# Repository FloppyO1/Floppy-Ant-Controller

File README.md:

# Floppy Ant Controller

The Floppy Ant Controller is a control board for Antweight (150g) fighting robots. It implements many features and thanks to the ability to change settings without having to modify the code it makes it perfect for less experienced people.

Taking inspiration from the now well-known Malenki nano (https://github.com/MarkR42/malenki-nano.git), other features have been added, maintaining a small size and an affordable price.

## Features

- 3x DC motors driver (1000 speed steps);
- 2x servo outputs (one of which can be selected with a soldering jumper if 5V or HV from the battery);
- 200Hz servo frequency;
- BEC 5V 3A max;
- 2x expansion ports with possible digital or analog readout (e.g. potentiometers, switches etc.);
- Support for 1 and 2s batteries;
- Battery voltage readout, with settable weapon speed limitation threshold & cutoff threshold (indipendent);
- Settings can be set via USB with dedicated software or serial terminal;
- 4 channels PWM, and 8 channels PPM compatibility;
- Dimensions of 23mm*33mm for a weight of 2.9g.

## Last hardware version notes (V1.3)
In the latest version (V1.3), problems with errors in the schematic were fixed, specifically a capacitor in the Buck Converter that prevented it from functioning correctly.

Compared to version 1.2, the battery and switch connections have been moved, because in their previous position they were too close to the receiver connections, so there was a risk of short circuits and burning out the entire 3.3V part (which happened to me😢).

## Software notes:

The FAC settings tool has been completely rewritten, this time not using phython and pysimplegui (which I discovered ask for a monthly fee to be distributed 😑).

This new version, signed with the 2.0 signature, is much more stable and looks better in my opinion. Like the previous version, it allows you to export and import all your settings in a .csv file for easy sharing.

## Support this project with a donation

To support this project you can make a donation via PayPal or buy a Floppy Ant Controller:

- https://www.paypal.com/paypalme/floppylab

- https://ko-fi.com/floppylab

## License
[CERN Open Hardware Licence Version 2 - Strongly Reciprocal](https://choosealicense.com/licenses/cern-ohl-s-2.0/#)

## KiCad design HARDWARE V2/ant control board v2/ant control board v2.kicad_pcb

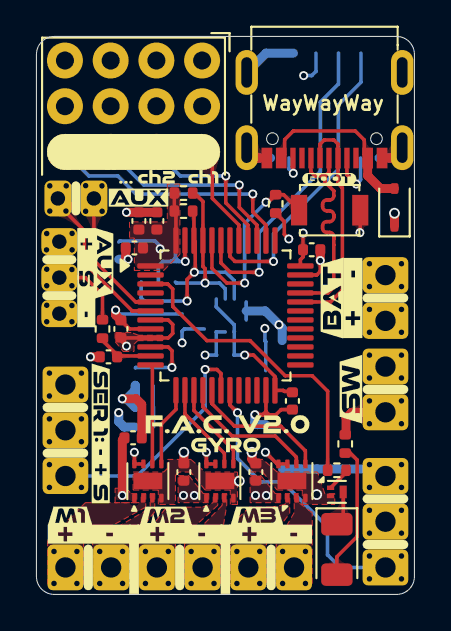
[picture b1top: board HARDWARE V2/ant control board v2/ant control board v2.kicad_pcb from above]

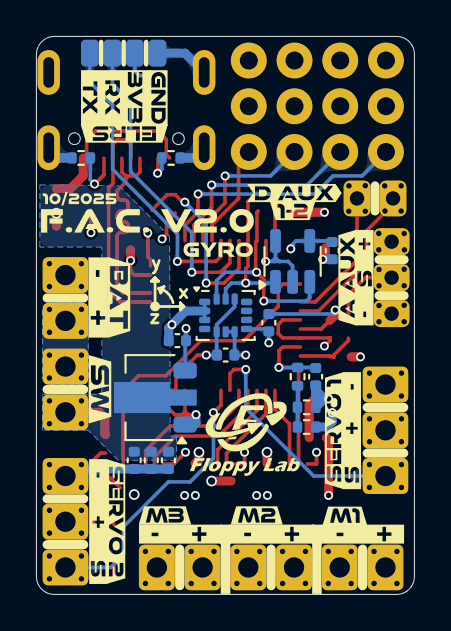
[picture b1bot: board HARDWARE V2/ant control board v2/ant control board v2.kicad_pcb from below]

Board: 4 copper layers, 21.0 x 31.0 mm, 96 parts (42 on the bottom side), 42 nets.

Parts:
C1, C2, C3, C4, C5, C6, C7, C8, C13: 4.7u; C_0402_1005Metric
C9, C10, C11, C14, C15, C16, C17, C18, C19: 100n; C_0402_1005Metric
D1: 1N5819WS; D_SOD-323
D2: STATUS; LED_1206_3216Metric
J1: SWITCH; 01x02_TH_pad_renforced
J2: 2s Battery; 01x02_TH_pad_renforced
J3: USB-C_304A-ACP16X; USB_C_304A-ACP16X
J4: M1; 01x02_TH_pad_renforced
J5: M2; 01x02_TH_pad_renforced
J6: M3; 01x02_TH_pad_renforced
J7: servo 1; 01x03_TH_pad_renforced
J8: servo 2; 01x03_TH_pad_renforced
J9: ADC_AUX; 01x03_TH_pad_renforced_small
J10: DIGITAL_AUX; 01x02_TH_pad_renforced_small
J12: ELRS; Pad 01x04 small
Q1: NMOS; Diodes_DFN1006-3
R1, R2, R6, R7, R8, R9, R10: 5.1k; R_0402_1005Metric
R3, R5: 10k; R_0402_1005Metric
R4, R11: 1.5k; R_0402_1005Metric
SW1: BOOT; SW_SPST_B3U-1000P
U1: GM7333; SOT-89-3
U2, U3, U4: DRV8837; WSON-8-1EP_2x2mm_P0.5mm_EP0.9x1.6mm
U5: LSM6DS3; LGA-14_3x2.5mm_P0.5mm_LayoutBorder3x4y
U6: STM32F072CBTx; LQFP-48_7x7mm_P0.5mm
U7: FS2A 4CH reciever
U8: AT24C02C; SOT-23-5
kibuzzard-68CD6E18, kibuzzard-68CD6E18#2: G***; kibuzzard-68CD6E18
kibuzzard-68CD6E40: G***; kibuzzard-68CD6E40
kibuzzard-68CD6E53, kibuzzard-68CD6E53#2: G***; kibuzzard-68CD6E53
kibuzzard-68CD7A1F: G***; kibuzzard-68CD7A1F
kibuzzard-68CD7CD9, kibuzzard-68CD7CD9#2: G***; kibuzzard-68CD7CD9
kibuzzard-68CD71AA, kibuzzard-68CD71AA#2: G***; kibuzzard-68CD71AA
kibuzzard-68CD73CB: G***; kibuzzard-68CD73CB
kibuzzard-68CD73D1: G***; kibuzzard-68CD73D1
kibuzzard-68CD78A4: G***; kibuzzard-68CD78A4
kibuzzard-68CD78BE: G***; kibuzzard-68CD78BE
kibuzzard-68CD78F0: G***; kibuzzard-68CD78F0
kibuzzard-68CD79A4: G***; kibuzzard-68CD79A4
kibuzzard-68CD79BE: G***; kibuzzard-68CD79BE
kibuzzard-68CD717E: G***; kibuzzard-68CD717E
kibuzzard-68CD725D, kibuzzard-68CD725D#2: G***; kibuzzard-68CD725D
kibuzzard-68CD756A: G***; kibuzzard-68CD756A
kibuzzard-68CD769D: G***; kibuzzard-68CD769D
kibuzzard-68CD784B: G***; kibuzzard-68CD784B
kibuzzard-68CD787F: G***; kibuzzard-68CD787F
kibuzzard-68CD793B: G***; kibuzzard-68CD793B
kibuzzard-68CD795A: G***; kibuzzard-68CD795A
kibuzzard-68CD7254, kibuzzard-68CD7254#2: G***; kibuzzard-68CD7254
kibuzzard-68CD7457: G***; kibuzzard-68CD7457
kibuzzard-68CD7642: G***; kibuzzard-68CD7642
kibuzzard-68CFBDBE: G***; kibuzzard-68CFBDBE
kibuzzard-68CFBDCF: G***; kibuzzard-68CFBDCF
kibuzzard-68CFBDD6: G***; kibuzzard-68CFBDD6
kibuzzard-68CFBE33: G***; kibuzzard-68CFBE33
kibuzzard-68CFBFAF: G***; kibuzzard-68CFBFAF
kibuzzard-68CFBFFE: G***; kibuzzard-68CFBFFE
kibuzzard-68CFC012: G***; kibuzzard-68CFC012
kibuzzard-68CFC153: G***; kibuzzard-68CFC153
kibuzzard-68CFCF3D: G***; kibuzzard-68CFCF3D
kibuzzard-68CFCF36: G***; kibuzzard-68CFCF36
kibuzzard-68CFCF49: G***; kibuzzard-68CFCF49
kibuzzard-68CFD0CD: G***; kibuzzard-68CFD0CD
kibuzzard-68CFD0E9: G***; kibuzzard-68CFD0E9
kibuzzard-6901144A: G***; kibuzzard-6901144A

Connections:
+3V3: C4.1, C9.1, C10.1, C13.1, C14.1, C15.1, C16.1, C17.1, C18.1, C19.1, J9.1, J12.3, R8.2, R9.2, SW1.1, U1.3 (OUT), U2.7 (~SLEEP), U2.8 (VCC), U3.7 (~SLEEP), U3.8 (VCC), U4.7 (~SLEEP), U4.8 (VCC), U5.5 (VDDIO), U5.8 (VDD), U5.12 (CS), U6.1 (VBAT), U6.7 (NRST), U6.9 (VDDA), U6.24 (VDD), U6.36 (VDDIO2), U6.48 (VDD), U7.2 (VCC), U7.5, U7.8, U7.11, U8.4 (VCC)
+BATT: C1.1, C2.1, C3.1, C5.1, C6.1, C7.1, D1.1 (K), J1.2, J7.2, J8.2, R3.1, R11.2, U1.2 (IN), U2.1 (VM), U3.1 (VM), U4.1 (VM)
/DC Motors/M1+: J4.1, U2.2 (OUT1)
/DC Motors/M1-: J4.2, U2.3 (OUT2)
/DC Motors/M2+: J5.1, U3.2 (OUT1)
/DC Motors/M2-: J5.2, U3.3 (OUT2)
/DC Motors/M3+: J6.1, U4.2 (OUT1)
/DC Motors/M3-: J6.2, U4.3 (OUT2)
/DC Motors/PWM_M1_B: U2.5 (IN2), U6.13 (PA3)
/DC Motors/PWM_M1_F: U2.6 (IN1), U6.12 (PA2)
/DC Motors/PWM_M2_B: U3.5 (IN2), U6.15 (PA5)
/DC Motors/PWM_M2_F: U3.6 (IN1), U6.14 (PA4)
/DC Motors/PWM_M3_B: U4.5 (IN2), U6.17 (PA7)
/DC Motors/PWM_M3_F: U4.6 (IN1), U6.16 (PA6)
/MCU and RX/ADC1: C11.2, R6.2, U6.11 (ADC_IN1)
/MCU and RX/BOOT0: R7.1, SW1.2, U6.44 (BOOT0)
/MCU and RX/CH1_PPM: U6.41 (PB5), U7.3 (CH1_(PPM))
/MCU and RX/CH2: U6.40 (PB4), U7.6 (CH2)
/MCU and RX/CH3: U6.39 (PB3), U7.9 (CH3)
/MCU and RX/CH4: U6.38 (PA15), U7.12 (CH4)
/MCU and RX/DIGITAL_AUX1: J10.1, U6.5 (PF0)
/MCU and RX/DIGITAL_AUX2: J10.2, U6.6 (PF1)
/MCU and RX/I2C1_SCL: R9.1, U5.13 (SCL), U6.45 (I2C1_SCL), U8.1 (SCL)
/MCU and RX/I2C1_SDA: R8.1, U5.14 (SDA), U6.46 (I2C1_SDA), U8.3 (SDA)
/MCU and RX/SERVO1: J7.1, U6.18 (PB0)
/MCU and RX/SERVO2: J8.1, U6.19 (PB1)
/MCU and RX/STATUS_LED: R10.1, U6.3 (PC14)
/MCU and RX/UART2_RX: J12.2, U6.43 (USART1_RX)
/MCU and RX/UART2_TX: J12.1, U6.42 (USART1_TX)
/MCU and RX/USB_D+: J3.6 (DP1), J3.8 (DP2), U6.33 (USB_DP)
/MCU and RX/USB_D-: J3.5 (DN2), J3.7 (DN1), U6.32 (USB_DM)
/MCU and RX/VBAT: C8.2, R5.2, U6.10 (ADC_IN0)
/Power/+SW: J1.1, J2.2
/Power/VUSB: D1.2 (A), J3.2 (VBUS), J3.11 (VBUS)
/Sensors/VBAT_DIV: R3.2, R4.1, R5.1
GND: C1.2, C2.2, C3.2, C4.2, C5.2, C6.2, C7.2, C8.1, C9.2, C10.2, C11.1, C13.2, C14.2, C15.2, C16.2, C17.2, C18.2, C19.2, J2.1, J3.1 (GND_1), J3.12 (GND_2), J3.13 (SHIELD), J7.3, J8.3, J9.3, J12.4, Q1.2 (S), R1.2, R2.2, R4.2, R7.2, U1.1 (GND), U2.4 (GND), U2.9 (GND), U3.4 (GND), U3.9 (GND), U4.4 (GND), U4.9 (GND), U5.1 (SDO/SA0), U5.2 (SDX), U5.3 (SCX), U5.6 (GND), U5.7 (GND), U6.8 (VSSA), U6.23 (VSS), U6.35 (VSS), U6.47 (VSS), U7.1 (GND), U7.4, U7.7, U7.10, U8.2 (GND), U8.5 (WP)
unnamed: D2.2 (A), R11.1
unnamed: D2.1 (K), Q1.3 (D)
unnamed: J3.4 (CC1), R2.1
unnamed: J3.10 (CC2), R1.1
unnamed: J9.2, R6.1
unnamed: Q1.1 (G), R10.2

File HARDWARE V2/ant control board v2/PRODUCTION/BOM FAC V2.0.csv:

"Reference","Value","LCSC","Footprint","Qty"
"U8","AT24C02C","C7432363","Package_TO_SOT_SMD:SOT-23-5","1"
"J3","USB-C_304A-ACP16X","C2909609","_MIA footprint:USB_C_304A-ACP16X","1"
"SW1","BOOT","C2885149","Button_Switch_SMD:SW_SPST_B3U-1000P","1"
"Q1","PNM3FD20V1E","C2875806","Package_DFN_QFN:Diodes_DFN1006-3","1"
"C2-C3-C4-C5-C6-C7-C8-C13","4.7u","C2858031","Capacitor_SMD:C_0402_1005Metric","8"
"U1","GM7333","C2833582","Package_TO_SOT_SMD:SOT-89-3","1"
"U5","LSM6DS3","C967633","Package_LGA:LGA-14_3x2.5mm_P0.5mm_LayoutBorder3x4y","1"
"D2","STATUS","C779809","LED_SMD:LED_1206_3216Metric","1"
"D1","1N5819WS","C191023","Diode_SMD:D_SOD-323","1"
"R11","220","C112291","Resistor_SMD:R_0402_1005Metric","1"
"U6","STM32F072CBTx","C81720","Package_QFP:LQFP-48_7x7mm_P0.5mm","1"
"R3-R5","10k","C60490","Resistor_SMD:R_0402_1005Metric","2"
"U2-U3-U4","DRV8837","C39159","Package_SON:WSON-8-1EP_2x2mm_P0.5mm_EP0.9x1.6mm","3"
"R1-R2-R6-R7-R8-R9-R10","5.1k","C25905","Resistor_SMD:R_0402_1005Metric","7"
"R4","1.5k","C25867","Resistor_SMD:R_0402_1005Metric","1"
"C9-C10-C11-C14-C15-C16-C17-C18-C19","100n","C1525","Capacitor_SMD:C_0402_1005Metric","9"

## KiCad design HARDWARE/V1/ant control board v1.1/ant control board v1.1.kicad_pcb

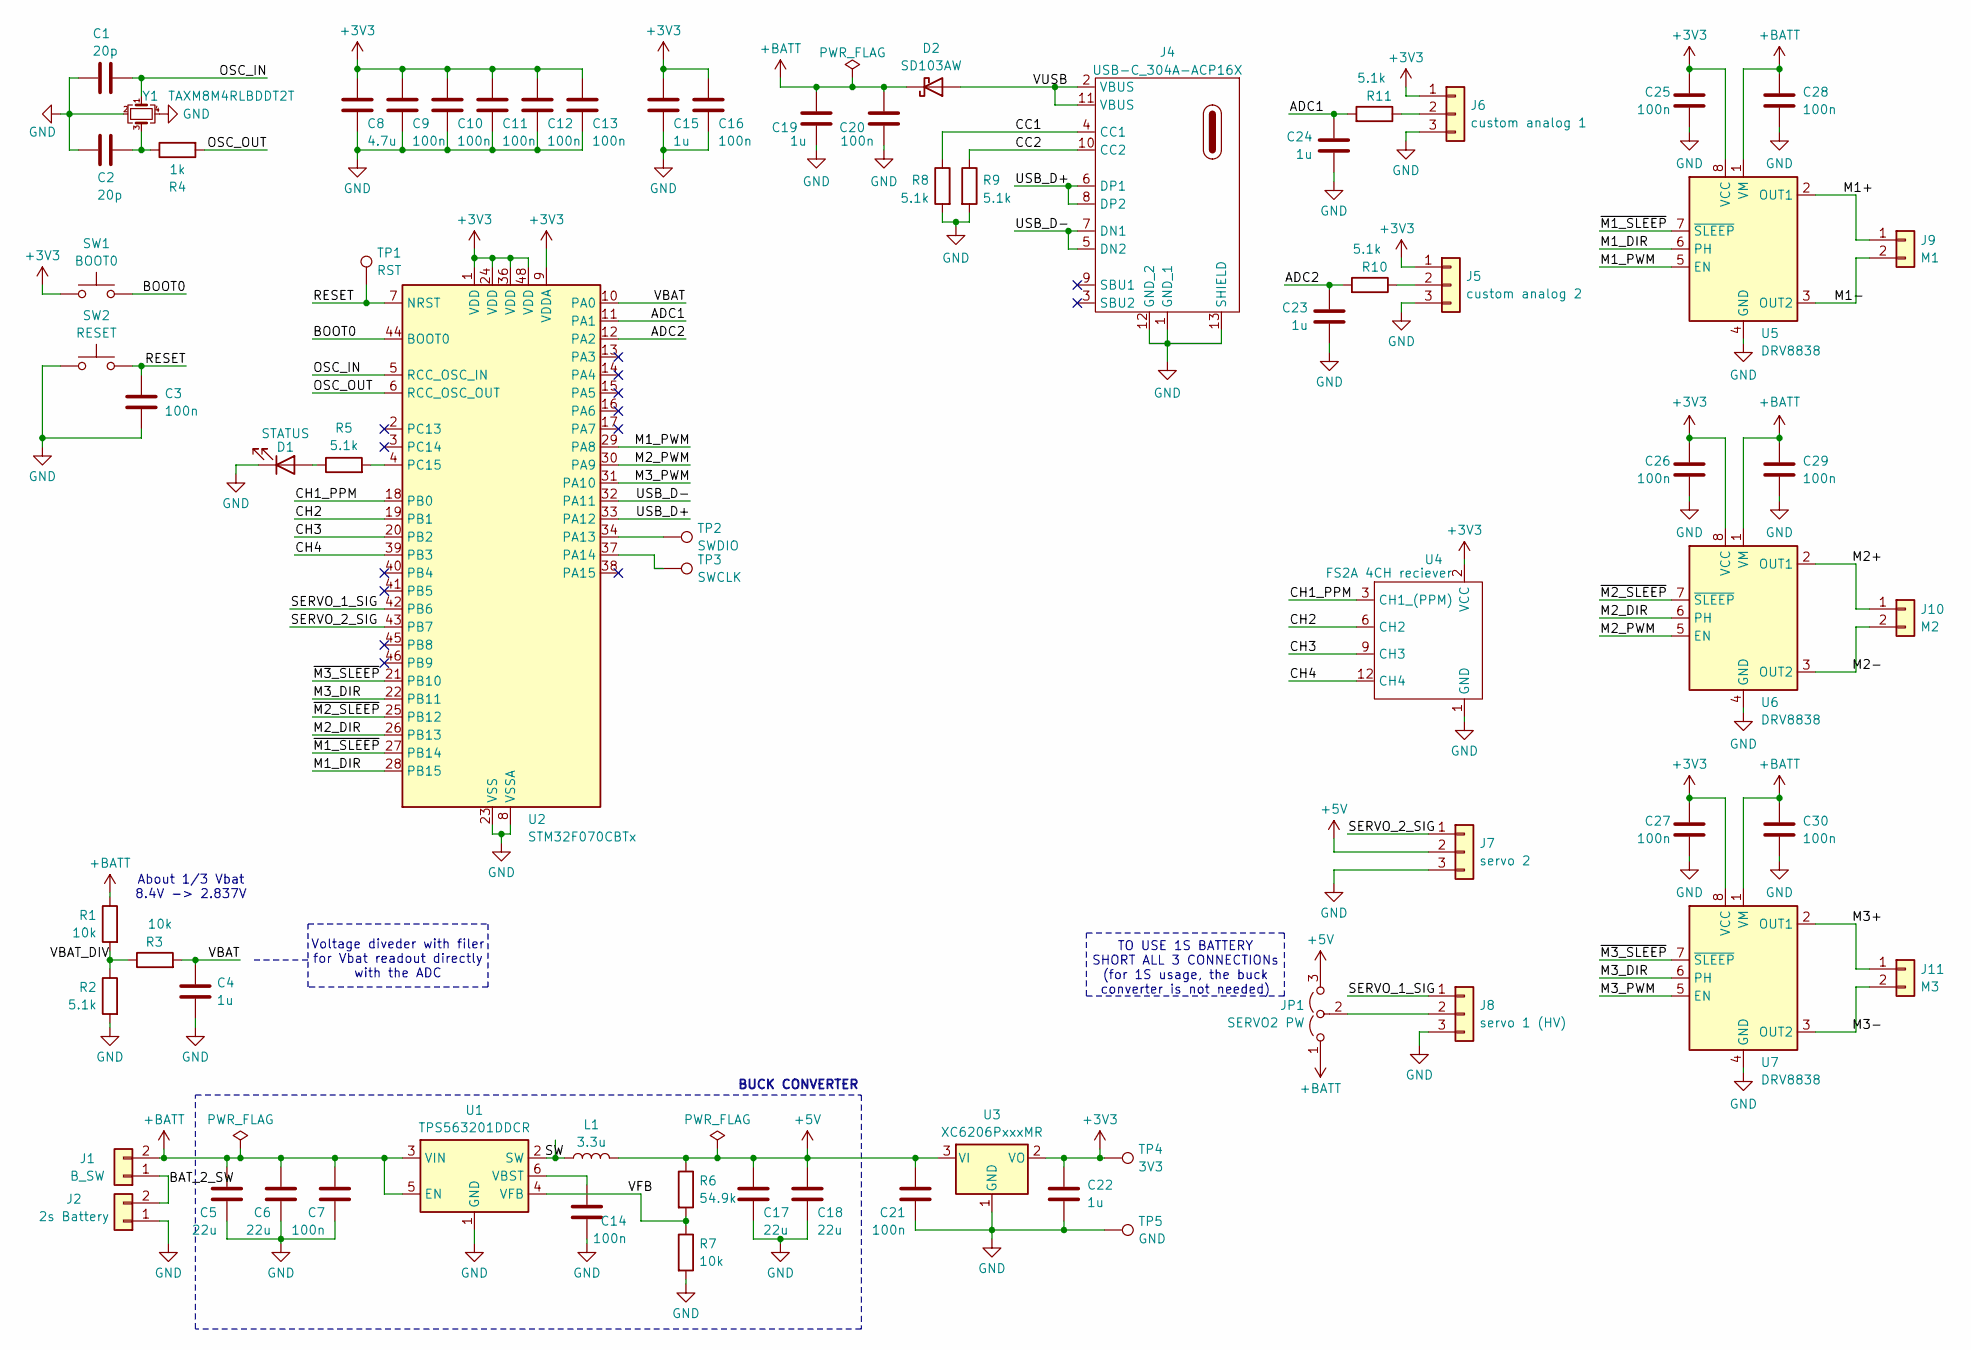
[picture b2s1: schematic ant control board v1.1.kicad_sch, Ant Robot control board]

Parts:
C1, C2: 20p; C_0603_1608Metric; LCSC C91702
C3, C7, C9, C10, C11, C12, C13, C14, C16, C20, C21, C25, C26, C27, C28, C29, C30: 100n; C_0603_1608Metric; LCSC C282519
C4, C15, C19, C22, C23, C24: 1u; C_0603_1608Metric; LCSC C1592
C5, C6, C17, C18: 22u; C_0603_1608Metric; LCSC C86295
C8: 4.7u; C_0603_1608Metric; LCSC C307467
D1: STATUS; LED_0805_2012Metric; LCSC C84259
D2: SD103AW; D_SOD-123; LCSC C181207
J1: B_SW; Pad 02x01
J2: 2s Battery; Pad 02x01
J4: USB-C_304A-ACP16X; USB_C_304A-ACP16X; LCSC C2909609
J5: custom analog 2; Pad 03x01
J6: custom analog 1; Pad 03x01
J7: servo 2; Pad 03x01
J8: servo 1 (HV); Pad 03x01
J9: M1; Pad 02x01
J10: M2; Pad 02x01
J11: M3; Pad 02x01
JP1: SERVO2 PW; SolderJumper-3_P1.3mm_Open_RoundedPad1.0x1.5mm_NumberLabels
L1: 3.3u; XRCD43-3R3M; LCSC C5289396
R1, R3, R7: 10k; R_0603_1608Metric; LCSC C103199
R2, R5, R8, R9, R10, R11: 5.1k; R_0603_1608Metric; LCSC C23186
R4: 1k; R_0603_1608Metric; LCSC C103198
R6: 54.9k; R_0603_1608Metric; LCSC C23077
SW1: BOOT0; SW-SMD_TS24CA SMD BUTTO 90deg; LCSC C393942
SW2: RESET; SW-SMD_TS24CA SMD BUTTO 90deg; LCSC C393942
TP1: RST; TestPoint_Pad_D1.0mm
TP2: SWDIO; TestPoint_Pad_D1.0mm
TP3: SWCLK; TestPoint_Pad_D1.0mm
TP4: 3V3; TestPoint_Pad_D1.0mm
TP5: GND; TestPoint_Pad_D1.0mm
U1: TPS563201DDCR; SOT-23-6; LCSC C116592
U2: STM32F070CBTx; LQFP-48_7x7mm_P0.5mm; LCSC C74909
U3: XC6206PxxxMR; SOT-23-3; LCSC C5148692
U4: FS2A 4CH reciever
U5, U6, U7: DRV8838; WSON-8-1EP_2x2mm_P0.5mm_EP0.9x1.6mm; LCSC C86667
Y1: TAXM8M4RLBDDT2T; Crystal_SMD_3225-4Pin_3.2x2.5mm; LCSC C720915

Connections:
+3V3: C8.1, C9.1, C10.1, C11.1, C12.1, C13.1, C15.1, C16.1, C22.1, C25.1, C26.1, C27.1, J5.1, J6.1, SW1.1, TP4.1, U2.1 (VDD), U2.9 (VDDA), U2.24 (VDD), U2.36 (VDD), U2.48 (VDD), U3.2 (VO), U4.2 (VCC), U4.5, U4.8, U4.11, U5.8 (VCC), U6.8 (VCC), U7.8 (VCC)
+5V: C17.1, C18.1, C21.1, J7.2, JP1.3 (B), L1.2, R6.1, U3.3 (VI)
+BATT: C5.1, C6.1, C7.1, C19.1, C20.1, C28.1, C29.1, C30.1, D2.1 (K), J1.2, JP1.1 (A), R1.1, U1.3 (VIN), U1.5 (EN), U5.1 (VM), U6.1 (VM), U7.1 (VM)
/ADC1: C24.2, R11.2, U2.11 (PA1)
/ADC2: C23.2, R10.2, U2.12 (PA2)
/BAT_2_SW: J1.1, J2.2
/BOOT0: SW1.2, U2.44 (BOOT0)
/CC1: J4.4 (CC1), R8.1
/CC2: J4.10 (CC2), R9.1
/CH1_PPM: U2.18 (PB0), U4.3 (CH1_(PPM))
/CH2: U2.19 (PB1), U4.6 (CH2)
/CH3: U2.20 (PB2), U4.9 (CH3)
/CH4: U2.39 (PB3), U4.12 (CH4)
/M1+: J9.1, U5.2 (OUT1)
/M1-: J9.2, U5.3 (OUT2)
/M1_DIR: U2.28 (PB15), U5.6 (PH)
/M1_PWM: U2.29 (PA8), U5.5 (EN)
/M2+: J10.1, U6.2 (OUT1)
/M2-: J10.2, U6.3 (OUT2)
/M2_DIR: U2.26 (PB13), U6.6 (PH)
/M2_PWM: U2.30 (PA9), U6.5 (EN)
/M3+: J11.1, U7.2 (OUT1)
/M3-: J11.2, U7.3 (OUT2)
/M3_DIR: U2.22 (PB11), U7.6 (PH)
/M3_PWM: U2.31 (PA10), U7.5 (EN)
/OSC_IN: C1.1, U2.5 (RCC_OSC_IN), Y1.1
/OSC_OUT: R4.2, U2.6 (RCC_OSC_OUT)
/RESET: C3.1, SW2.2, TP1.1, U2.7 (NRST)
/SERVO_1_SIG: J8.1, U2.42 (PB6)
/SERVO_2_SIG: J7.1, U2.43 (PB7)
/SW: L1.1, U1.2 (SW)
/USB_D+: J4.6 (DP1), J4.8 (DP2), U2.33 (PA12)
/USB_D-: J4.5 (DN2), J4.7 (DN1), U2.32 (PA11)
/VBAT: C4.2, R3.2, U2.10 (PA0)
/VBAT_DIV: R1.2, R2.1, R3.1
/VFB: R6.2, R7.1, U1.4 (VFB)
/VUSB: D2.2 (A), J4.2 (VBUS), J4.11 (VBUS)
/~M1_SLEEP: U2.27 (PB14), U5.7 (~SLEEP)
/~M2_SLEEP: U2.25 (PB12), U6.7 (~SLEEP)
/~M3_SLEEP: U2.21 (PB10), U7.7 (~SLEEP)
GND: C1.2, C2.2, C3.2, C4.1, C5.2, C6.2, C7.2, C8.2, C9.2, C10.2, C11.2, C12.2, C13.2, C14.2, C15.2, C16.2, C17.2, C18.2, C19.2, C20.2, C21.2, C22.2, C23.1, C24.1, C25.2, C26.2, C27.2, C28.2, C29.2, C30.2, D1.1 (K), J2.1, J4.1 (GND_1), J4.12 (GND_2), J4.13 (SHIELD), J5.3, J6.3, J7.3, J8.3, R2.2, R7.2, R8.2, R9.2, SW1.3, SW1.4, SW2.1, SW2.3, SW2.4, TP5.1, U1.1 (GND), U2.8 (VSSA), U2.23 (VSS), U2.35 (VSS), U2.47 (VSS), U3.1 (GND), U4.1 (GND), U4.4, U4.7, U4.10, U5.4 (GND), U5.9 (GND), U6.4 (GND), U6.9 (GND), U7.4 (GND), U7.9 (GND), Y1.2, Y1.4
unnamed: C2.1, R4.1, Y1.3
unnamed: D1.2 (A), R5.1
unnamed: J5.2, R10.1
unnamed: J6.2, R11.1
unnamed: J8.2, JP1.2 (C)
unnamed: C14.1, U1.6 (VBST)
unnamed: TP2.1, U2.34 (PA13)
unnamed: TP3.1, U2.37 (PA14)
unnamed: R5.2, U2.4 (PC15)

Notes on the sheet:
TO USE 1S BATTERY SHORT ALL 3 CONNECTIONs (for 1S usage, the buck converter is not needed)
About 1/3 Vbat 8.4V -> 2.837V
Voltage diveder with filer for Vbat readout directly with the ADC
BUCK CONVERTER

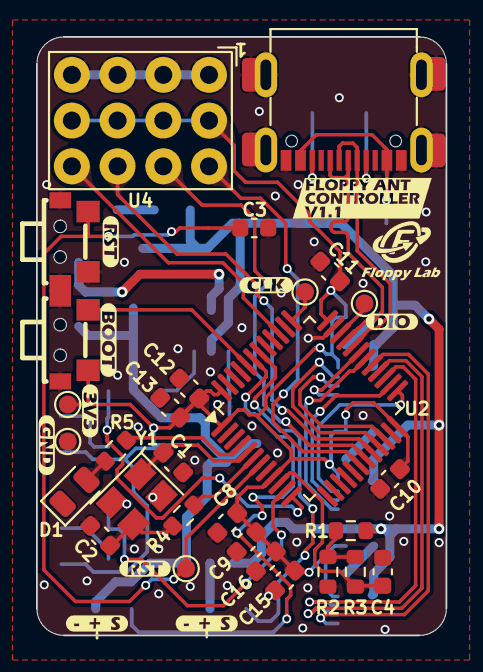
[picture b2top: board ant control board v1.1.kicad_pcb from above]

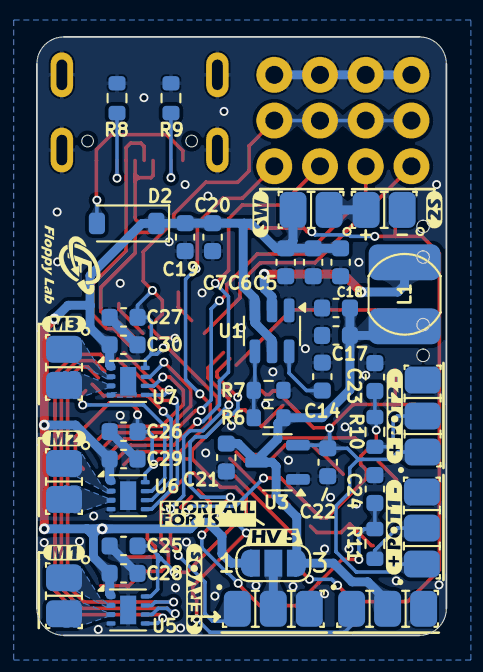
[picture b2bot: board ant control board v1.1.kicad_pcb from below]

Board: 2 copper layers, 22.8 x 33.2 mm, 90 parts (51 on the bottom side), 50 nets.

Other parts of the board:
kibuzzard-667D9F0F: G***; kibuzzard-667D9F0F
kibuzzard-667D9F1D: G***; kibuzzard-667D9F1D
kibuzzard-667D9F2A: G***; kibuzzard-667D9F2A
kibuzzard-667D9F03: G***; kibuzzard-667D9F03
kibuzzard-667D9F6F: G***; kibuzzard-667D9F6F
kibuzzard-667D9F7A: G***; kibuzzard-667D9F7A
kibuzzard-667D9F7E: G***; kibuzzard-667D9F7E
kibuzzard-667D9F8D: G***; kibuzzard-667D9F8D
kibuzzard-667D9F19: G***; kibuzzard-667D9F19
kibuzzard-667D9F22: G***; kibuzzard-667D9F22
kibuzzard-667D9F56: G***; kibuzzard-667D9F56
kibuzzard-667D9F67: G***; kibuzzard-667D9F67
kibuzzard-667D9F87: G***; kibuzzard-667D9F87
kibuzzard-667D9F91: G***; kibuzzard-667D9F91
kibuzzard-667D9F97: G***; kibuzzard-667D9F97
kibuzzard-667D9FA0: G***; kibuzzard-667D9FA0
kibuzzard-667D9FA9: G***; kibuzzard-667D9FA9
kibuzzard-667D9FAD: G***; kibuzzard-667D9FAD
kibuzzard-667D9FB5: G***; kibuzzard-667D9FB5
kibuzzard-667EE2AA: G***; kibuzzard-667EE2AA

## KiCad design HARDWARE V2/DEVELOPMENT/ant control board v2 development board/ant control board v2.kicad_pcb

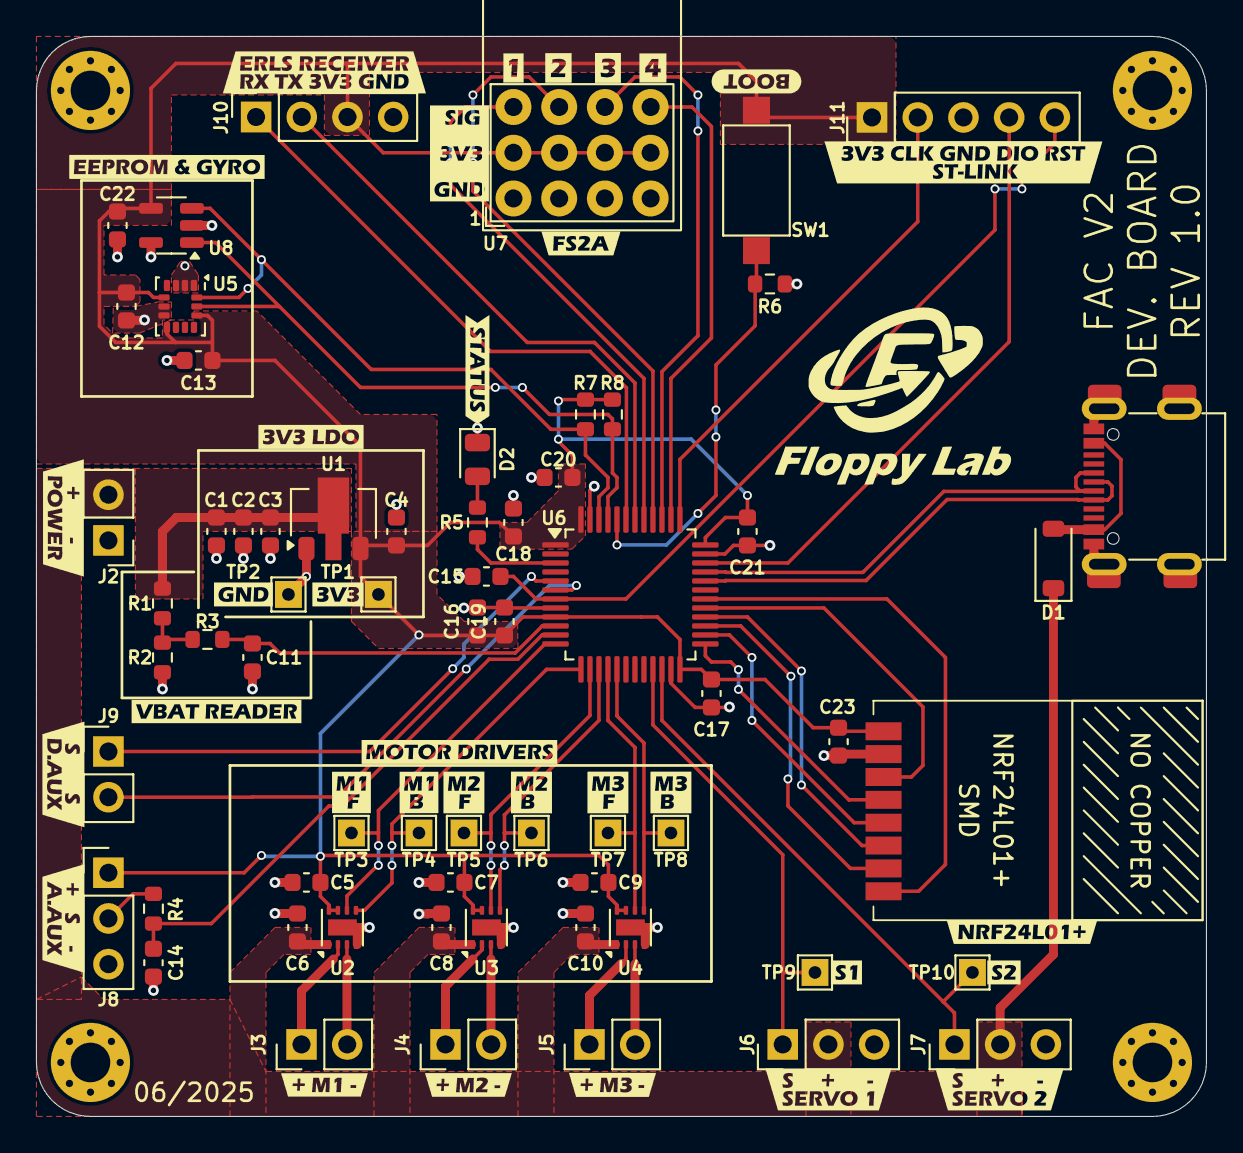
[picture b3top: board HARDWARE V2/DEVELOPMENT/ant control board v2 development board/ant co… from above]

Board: 2 copper layers, 65.0 x 60.0 mm, 101 parts (0 on the bottom side), 46 nets.

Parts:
C1, C2, C3, C4, C6, C8, C10, C11, C16, C23: 4.7u; C_0603_1608Metric
C5, C7, C9, C12, C13, C14, C15, C17, C18, C19, C20, C21, C22: 100n; C_0603_1608Metric
D1: SD103AWS; D_SOD-123
D2: STATUS; LED_0805_2012Metric
H1, H2, H3, H4: MountingHole; MountingHole_2.2mm_M2_Pad_Via
J1: USB-C_304A-ACP16X; USB_C_304A-ACP16X
J2: 2s Battery; PinHeader_1x02_P2.54mm_Vertical
J3: M1; PinHeader_1x02_P2.54mm_Vertical
J4: M2; PinHeader_1x02_P2.54mm_Vertical
J5: M3; PinHeader_1x02_P2.54mm_Vertical
J6: servo 1; PinHeader_1x03_P2.54mm_Vertical
J7: servo 2; PinHeader_1x03_P2.54mm_Vertical
J8: ADC_AUX; PinHeader_1x03_P2.54mm_Vertical
J9: DIGITAL_AUX; PinHeader_1x02_P2.54mm_Vertical
J10: ELRS; PinSocket_1x04_P2.54mm_Vertical
J11: ST-LINK; PinHeader_1x05_P2.54mm_Vertical
R1, R3: 10k; R_0603_1608Metric
R2, R5: 1.5k; R_0603_1608Metric
R4, R6, R7, R8: 5.1k; R_0603_1608Metric
SW1: BOOT; SW_SPST_CK_RS282G05A3
TP1: 3V3; TestPoint_THTPad_1.5x1.5mm_Drill0.7mm
TP2: GND; TestPoint_THTPad_1.5x1.5mm_Drill0.7mm
TP3: M1 IN1; TestPoint_THTPad_1.5x1.5mm_Drill0.7mm
TP4: M1 IN2; TestPoint_THTPad_1.5x1.5mm_Drill0.7mm
TP5: M2 IN1; TestPoint_THTPad_1.5x1.5mm_Drill0.7mm
TP6: M2 IN2; TestPoint_THTPad_1.5x1.5mm_Drill0.7mm
TP7: M3 IN1; TestPoint_THTPad_1.5x1.5mm_Drill0.7mm
TP8: M3 IN2; TestPoint_THTPad_1.5x1.5mm_Drill0.7mm
TP9: S1; TestPoint_THTPad_1.5x1.5mm_Drill0.7mm
TP10: S2; TestPoint_THTPad_1.5x1.5mm_Drill0.7mm
U1: GM7333; SOT-89-3
U2, U3, U4: DRV8837; WSON-8-1EP_2x2mm_P0.5mm_EP0.9x1.6mm
U5: LSM6DS3; LGA-14_3x2.5mm_P0.5mm_LayoutBorder3x4y
U6: STM32F072CBTx; LQFP-48_7x7mm_P0.5mm
U7: FS2A 4CH reciever
U8: AT24C02C; SOT-23-5
U9: NRF24L01; NRF24L01+ SMD
kibuzzard-68590DA6: G***; kibuzzard-68590DA6
kibuzzard-68590DB3: G***; kibuzzard-68590DB3
kibuzzard-68590DCB: G***; kibuzzard-68590DCB
kibuzzard-68590DDD: G***; kibuzzard-68590DDD
kibuzzard-68590DE3: G***; kibuzzard-68590DE3
kibuzzard-68590E11: G***; kibuzzard-68590E11
kibuzzard-68590E35: G***; kibuzzard-68590E35
kibuzzard-68590E57: G***; kibuzzard-68590E57
kibuzzard-68590F1F: G***; kibuzzard-68590F1F
kibuzzard-68590F5B: G***; kibuzzard-68590F5B
kibuzzard-68590F79: G***; kibuzzard-68590F79
kibuzzard-68591B9B: G***; kibuzzard-68591B9B
kibuzzard-68591B85: G***; kibuzzard-68591B85
kibuzzard-68591BA5: G***; kibuzzard-68591BA5
kibuzzard-68591BA8: G***; kibuzzard-68591BA8
kibuzzard-685910F4: G***; kibuzzard-685910F4
kibuzzard-685911E8: G***; kibuzzard-685911E8
kibuzzard-685911EF: G***; kibuzzard-685911EF
kibuzzard-685916F6: G***; kibuzzard-685916F6
kibuzzard-6859100F: G***; kibuzzard-6859100F
kibuzzard-6859102F: G***; kibuzzard-6859102F
kibuzzard-6859109F: G***; kibuzzard-6859109F
kibuzzard-6859111F: G***; kibuzzard-6859111F
kibuzzard-6859112C: G***; kibuzzard-6859112C
kibuzzard-6859119B: G***; kibuzzard-6859119B
kibuzzard-6859170A: G***; kibuzzard-6859170A
kibuzzard-68591052: G***; kibuzzard-68591052
kibuzzard-68591071: G***; kibuzzard-68591071
kibuzzard-68591112: G***; kibuzzard-68591112
kibuzzard-68591123: G***; kibuzzard-68591123
kibuzzard-68591131: G***; kibuzzard-68591131
kibuzzard-68591152: G***; kibuzzard-68591152
kibuzzard-68591192: G***; kibuzzard-68591192

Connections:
+3V3: C4.1, C5.1, C7.1, C9.1, C12.1, C13.1, C16.1, C17.1, C18.1, C19.1, C20.1, C21.1, C22.1, C23.1, J8.1, J10.3, J11.1, R7.2, R8.2, SW1.1, TP1.1, U1.3 (OUT), U2.7 (~SLEEP), U2.8 (VCC), U3.7 (~SLEEP), U3.8 (VCC), U4.7 (~SLEEP), U4.8 (VCC), U5.5 (VDDIO), U5.8 (VDD), U5.12 (CS), U6.1 (VBAT), U6.9 (VDDA), U6.24 (VDD), U6.36 (VDDIO2), U6.48 (VDD), U7.2 (VCC), U7.5, U7.8, U7.11, U8.4 (VCC), U9.1 (VCC)
+BATT: C1.1, C2.1, C3.1, C6.1, C8.1, C10.1, D1.1 (K), J2.2, J6.2, J7.2, R1.1, U1.2 (IN), U2.1 (VM), U3.1 (VM), U4.1 (VM)
/DC Motors/M1+: J3.1, U2.2 (OUT1)
/DC Motors/M1-: J3.2, U2.3 (OUT2)
/DC Motors/M2+: J4.1, U3.2 (OUT1)
/DC Motors/M2-: J4.2, U3.3 (OUT2)
/DC Motors/M3+: J5.1, U4.2 (OUT1)
/DC Motors/M3-: J5.2, U4.3 (OUT2)
/DC Motors/PWM_M1_B: TP4.1, U2.5 (IN2), U6.13 (PA3)
/DC Motors/PWM_M1_F: TP3.1, U2.6 (IN1), U6.12 (PA2)
/DC Motors/PWM_M2_B: TP6.1, U3.5 (IN2), U6.15 (PA5)
/DC Motors/PWM_M2_F: TP5.1, U3.6 (IN1), U6.14 (PA4)
/DC Motors/PWM_M3_B: TP8.1, U4.5 (IN2), U6.17 (PA7)
/DC Motors/PWM_M3_F: TP7.1, U4.6 (IN1), U6.16 (PA6)
/MCU and RX/ADC1: C14.2, R4.2, U6.11 (ADC_IN1)
/MCU and RX/BOOT0: R6.1, SW1.2, U6.44 (BOOT0)
/MCU and RX/CH1_PPM: U6.41 (PB5), U7.3 (CH1_(PPM))
/MCU and RX/CH2: U6.40 (PB4), U7.6 (CH2)
/MCU and RX/CH3: U6.39 (PB3), U7.9 (CH3)
/MCU and RX/CH4: U6.38 (PA15), U7.12 (CH4)
/MCU and RX/DIGITAL_AUX1: J9.1, U6.5 (PF0)
/MCU and RX/DIGITAL_AUX2: J9.2, U6.6 (PF1)
/MCU and RX/I2C1_SCL: R8.1, U5.13 (SCL), U6.45 (I2C1_SCL), U8.1 (SCL)
/MCU and RX/I2C1_SDA: R7.1, U5.14 (SDA), U6.46 (I2C1_SDA), U8.3 (SDA)
/MCU and RX/NRF24L01_CE: U6.29 (PA8), U9.3 (CE)
/MCU and RX/NRF24L01_IRQ: U6.30 (PA9), U9.8 (IRQ)
/MCU and RX/RESET: C15.1, J11.5, U6.7 (NRST)
/MCU and RX/SERVO1: J6.1, TP9.1, U6.21 (TIM2_CH3)
/MCU and RX/SERVO2: J7.1, TP10.1, U6.22 (TIM2_CH4)
/MCU and RX/SPI2_MISO: U6.27 (SPI2_MISO), U9.7 (MISO)
/MCU and RX/SPI2_MOSI: U6.28 (SPI2_MOSI), U9.6 (MOSI)
/MCU and RX/SPI2_NSS: U6.25 (SPI2_NSS), U9.4 (~CS)
/MCU and RX/SPI2_SCK: U6.26 (SPI2_SCK), U9.5 (SCK)
/MCU and RX/STATUS_LED: R5.1, U6.3 (PC14)
/MCU and RX/SWCLK: J11.2, U6.37 (SYS_SWCLK)
/MCU and RX/SWDIO: J11.4, U6.34 (SYS_SWDIO)
/MCU and RX/UART2_RX: J10.1, U6.43 (USART1_RX)
/MCU and RX/UART2_TX: J10.2, U6.42 (USART1_TX)
/MCU and RX/USB_D+: J1.6 (DP1), J1.8 (DP2), U6.33 (USB_DP)
/MCU and RX/USB_D-: J1.5 (DN2), J1.7 (DN1), U6.32 (USB_DM)
/MCU and RX/VBAT: C11.2, R3.2, U6.10 (ADC_IN0)
/Power/VUSB: D1.2 (A), J1.2 (VBUS), J1.11 (VBUS)
/Sensors/VBAT_DIV: R1.2, R2.1, R3.1
GND: C1.2, C2.2, C3.2, C4.2, C5.2, C6.2, C7.2, C8.2, C9.2, C10.2, C11.1, C12.2, C13.2, C14.1, C15.2, C16.2, C17.2, C18.2, C19.2, C20.2, C21.2, C22.2, C23.2, D2.1 (K), J1.1 (GND_1), J1.12 (GND_2), J1.13 (SHIELD), J2.1, J6.3, J7.3, J8.3, J10.4, J11.3, R2.2, R6.2, TP2.1, U1.1 (GND), U2.4 (GND), U2.9 (GND), U3.4 (GND), U3.9 (GND), U4.4 (GND), U4.9 (GND), U5.1 (SDO/SA0), U5.2 (SDX), U5.3 (SCX), U5.6 (GND), U5.7 (GND), U6.8 (VSSA), U6.23 (VSS), U6.35 (VSS), U6.47 (VSS), U7.1 (GND), U7.4, U7.7, U7.10, U8.2 (GND), U8.5 (WP), U9.2 (GND)
unnamed: D2.2 (A), R5.2
unnamed: J8.2, R4.1

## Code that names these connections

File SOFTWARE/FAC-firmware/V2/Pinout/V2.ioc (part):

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Mcu.Name=STM32F072C(8-B)Tx
Mcu.Package=LQFP48
Mcu.UserName=STM32F072CBTx
PA0.GPIOParameters=GPIO_Label
PA0.GPIO_Label=VBAT
PA0.Mode=IN0
PA0.Signal=ADC_IN0
PA1.GPIOParameters=GPIO_Label
PA1.GPIO_Label=ADC_AUX
PA1.Mode=IN1
PA1.Signal=ADC_IN1
PA11.Mode=Device
PA11.Signal=USB_DM
PA12.Mode=Device
PA12.Signal=USB_DP
PA13.Mode=Serial_Wire
PA13.Signal=SYS_SWDIO
PA14.Mode=Serial_Wire
PA14.Signal=SYS_SWCLK
PA15.GPIOParameters=GPIO_Label
PA15.GPIO_Label=CH4
PA15.Signal=GPXTI15
PA2.GPIOParameters=GPIO_Label
PA2.GPIO_Label=M1_F
PA2.Signal=GPIO_Output
PA3.GPIOParameters=GPIO_Label
PA3.GPIO_Label=M1_B
PA3.Signal=GPIO_Output
PA4.GPIOParameters=GPIO_Label
PA4.GPIO_Label=M2_F
PA4.Signal=GPIO_Output
PA5.GPIOParameters=GPIO_Label
PA5.GPIO_Label=M2_B
PA5.Signal=GPIO_Output
PA6.GPIOParameters=GPIO_Label
PA6.GPIO_Label=M3_F
PA6.Signal=GPIO_Output
PA7.GPIOParameters=GPIO_Label
PA7.GPIO_Label=M3_B
PA7.Signal=GPIO_Output
PA8.GPIOParameters=GPIO_Label
PA8.GPIO_Label=NRF24L01_CE
PA8.Signal=GPIO_Output
PB10.GPIOParameters=GPIO_Label
PB10.GPIO_Label=SERVO1
PB10.Signal=S_TIM2_CH3
PB11.GPIOParameters=GPIO_Label
PB11.GPIO_Label=SERVO2
PB11.Signal=S_TIM2_CH4
PB12.Mode=NSS_Signal_Hard_Output
PB12.Signal=SPI2_NSS
PB13.Mode=Full_Duplex_Master
PB13.Signal=SPI2_SCK
PB14.Mode=Full_Duplex_Master
PB14.Signal=SPI2_MISO
PB15.Mode=Full_Duplex_Master
PB15.Signal=SPI2_MOSI
PB3.GPIOParameters=GPIO_Label
PB3.GPIO_Label=CH3
PB3.Signal=GPXTI3
PB4.GPIOParameters=GPIO_Label
PB4.GPIO_Label=CH2
PB4.Signal=GPXTI4
PB5.GPIOParameters=GPIO_Label
PB5.GPIO_Label=CH1
PB5.Signal=GPXTI5
PB6.Mode=Asynchronous
PB6.Signal=USART1_TX
PB7.Mode=Asynchronous
PB7.Signal=USART1_RX
PB8.Mode=I2C
PB8.Signal=I2C1_SCL
PB9.Mode=I2C
PB9.Signal=I2C1_SDA
PC14-OSC32_IN.GPIOParameters=GPIO_Label
PC14-OSC32_IN.GPIO_Label=LED
PC14-OSC32_IN.Signal=GPIO_Output
PF0-OSC_IN.GPIOParameters=GPIO_Label
PF0-OSC_IN.GPIO_Label=DIGITAL_AUX1
PF0-OSC_IN.Signal=GPXTI0
PF1-OSC_OUT.GPIOParameters=GPIO_Label
PF1-OSC_OUT.GPIO_Label=DIGITAL_AUX2
PF1-OSC_OUT.Signal=GPXTI1
RCC.SYSCLKFreq_VALUE=48000000
RCC.SYSCLKSource=RCC_SYSCLKSOURCE_HSI48
board=custom

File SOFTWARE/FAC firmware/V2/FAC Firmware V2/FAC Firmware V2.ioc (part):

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Mcu.Name=STM32F072C(8-B)Tx
Mcu.Package=LQFP48
Mcu.UserName=STM32F072CBTx
PA0.GPIOParameters=GPIO_Label
PA0.GPIO_Label=VBAT
PA0.Mode=IN0
PA0.Signal=ADC_IN0
PA1.GPIOParameters=GPIO_Label
PA1.GPIO_Label=ADC_AUX
PA1.Mode=IN1
PA1.Signal=ADC_IN1
PA11.Mode=Device
PA11.Signal=USB_DM
PA12.Mode=Device
PA12.Signal=USB_DP
PA13.Mode=Serial_Wire
PA13.Signal=SYS_SWDIO
PA14.Mode=Serial_Wire
PA14.Signal=SYS_SWCLK
PA15.GPIOParameters=GPIO_Label,GPIO_ModeDefaultEXTI
PA15.GPIO_Label=CH4
PA15.GPIO_ModeDefaultEXTI=GPIO_MODE_IT_RISING_FALLING
PA15.Signal=GPXTI15
PA2.GPIOParameters=GPIO_Label
PA2.GPIO_Label=M1_F
PA2.Signal=GPIO_Output
PA3.GPIOParameters=GPIO_Label
PA3.GPIO_Label=M1_B
PA3.Signal=GPIO_Output
PA4.GPIOParameters=GPIO_Label
PA4.GPIO_Label=M2_F
PA4.Signal=GPIO_Output
PA5.GPIOParameters=GPIO_Label
PA5.GPIO_Label=M2_B
PA5.Signal=GPIO_Output
PA6.GPIOParameters=GPIO_Label
PA6.GPIO_Label=M3_F
PA6.Signal=GPIO_Output
PA7.GPIOParameters=GPIO_Label
PA7.GPIO_Label=M3_B
PA7.Signal=GPIO_Output
PA8.GPIOParameters=GPIO_Label
PA8.GPIO_Label=NRF24L01_CE
PA8.Signal=GPIO_Output
PB0.GPIOParameters=GPIO_Label
PB0.GPIO_Label=SERVO1
PB0.Signal=S_TIM3_CH3
PB1.GPIOParameters=GPIO_Label
PB1.GPIO_Label=SERVO2
PB1.Signal=S_TIM3_CH4
PB12.Mode=NSS_Signal_Hard_Output
PB12.Signal=SPI2_NSS
PB13.Mode=Full_Duplex_Master
PB13.Signal=SPI2_SCK
PB14.Mode=Full_Duplex_Master
PB14.Signal=SPI2_MISO
PB15.Mode=Full_Duplex_Master
PB15.Signal=SPI2_MOSI
PB3.GPIOParameters=GPIO_Label,GPIO_ModeDefaultEXTI
PB3.GPIO_Label=CH3
PB3.GPIO_ModeDefaultEXTI=GPIO_MODE_IT_RISING_FALLING
PB3.Signal=GPXTI3
PB4.GPIOParameters=GPIO_Label,GPIO_ModeDefaultEXTI
PB4.GPIO_Label=CH2
PB4.GPIO_ModeDefaultEXTI=GPIO_MODE_IT_RISING_FALLING
PB4.Signal=GPXTI4
PB5.GPIOParameters=GPIO_Label,GPIO_ModeDefaultEXTI
PB5.GPIO_Label=CH1
PB5.GPIO_ModeDefaultEXTI=GPIO_MODE_IT_RISING_FALLING
PB5.Signal=GPXTI5
PB6.Mode=Asynchronous
PB6.Signal=USART1_TX
PB7.Mode=Asynchronous
PB7.Signal=USART1_RX
PB8.Mode=I2C
PB8.Signal=I2C1_SCL
PB9.Mode=I2C
PB9.Signal=I2C1_SDA
PC14-OSC32_IN.GPIOParameters=GPIO_Label
PC14-OSC32_IN.GPIO_Label=LED
PC14-OSC32_IN.Signal=GPIO_Output
PF0-OSC_IN.GPIOParameters=GPIO_Label
PF0-OSC_IN.GPIO_Label=DIGITAL_AUX1
PF0-OSC_IN.Signal=GPIO_Output
PF1-OSC_OUT.GPIOParameters=GPIO_Label
PF1-OSC_OUT.GPIO_Label=DIGITAL_AUX2
PF1-OSC_OUT.Signal=GPXTI1
RCC.SYSCLKFreq_VALUE=48000000
RCC.SYSCLKSource=RCC_SYSCLKSOURCE_PLLCLK
board=custom

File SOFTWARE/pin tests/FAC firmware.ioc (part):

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Mcu.Name=STM32F070CBTx
Mcu.Package=LQFP48
Mcu.UserName=STM32F070CBTx
PA0.GPIOParameters=GPIO_Label
PA0.GPIO_Label=VBAT
PA0.Mode=IN0
PA0.Signal=ADC_IN0
PA10.GPIOParameters=GPIO_Label
PA10.GPIO_Label=PWM_M3_F
PA10.Signal=GPIO_Output
PA11.Mode=Device
PA11.Signal=USB_DM
PA12.Mode=Device
PA12.Signal=USB_DP
PA13.Mode=Serial_Wire
PA13.Signal=SYS_SWDIO
PA14.Mode=Serial_Wire
PA14.Signal=SYS_SWCLK
PA2.Mode=Asynchronous
PA2.Signal=USART2_TX
PA3.Mode=Asynchronous
PA3.Signal=USART2_RX
PA4.GPIOParameters=GPIO_Label
PA4.GPIO_Label=POT1
PA4.Signal=ADC_IN4
PA5.GPIOParameters=GPIO_Label
PA5.GPIO_Label=POT2
PA5.Signal=ADC_IN5
PA8.GPIOParameters=GPIO_Label
PA8.GPIO_Label=PWM_M1_F
PA8.Signal=GPIO_Output
PA9.GPIOParameters=GPIO_Label
PA9.GPIO_Label=PWM_M2_F
PA9.Signal=GPIO_Output
PB0.GPIOParameters=GPIO_PuPd,GPIO_Label,GPIO_ModeDefaultEXTI
PB0.GPIO_Label=CH1
PB0.GPIO_ModeDefaultEXTI=GPIO_MODE_IT_RISING_FALLING
PB0.GPIO_PuPd=GPIO_PULLUP
PB0.Signal=GPXTI0
PB1.GPIOParameters=GPIO_PuPd,GPIO_Label,GPIO_ModeDefaultEXTI
PB1.GPIO_Label=CH2
PB1.GPIO_ModeDefaultEXTI=GPIO_MODE_IT_FALLING
PB1.GPIO_PuPd=GPIO_PULLUP
PB1.Signal=GPXTI1
PB10.GPIOParameters=GPIO_Label
PB10.GPIO_Label=SLEEPN_M3
PB10.Signal=GPIO_Output
PB11.GPIOParameters=GPIO_Label
PB11.GPIO_Label=PWM_M3_B
PB11.Signal=GPIO_Output
PB12.GPIOParameters=GPIO_Label
PB12.GPIO_Label=SLEEPN_M2
PB12.Signal=GPIO_Output
PB13.GPIOParameters=GPIO_Label
PB13.GPIO_Label=PWM_M2_B
PB13.Signal=GPIO_Output
PB14.GPIOParameters=GPIO_Label
PB14.GPIO_Label=SLEEPN_M1
PB14.Signal=GPIO_Output
PB15.GPIOParameters=GPIO_Label
PB15.GPIO_Label=PWM_M1_B
PB15.Signal=GPIO_Output
PB2.GPIOParameters=GPIO_PuPd,GPIO_Label,GPIO_ModeDefaultEXTI
PB2.GPIO_Label=CH3
PB2.GPIO_ModeDefaultEXTI=GPIO_MODE_IT_FALLING
PB2.GPIO_PuPd=GPIO_PULLUP
PB2.Signal=GPXTI2
PB3.GPIOParameters=GPIO_PuPd,GPIO_Label,GPIO_ModeDefaultEXTI
PB3.GPIO_Label=CH4
PB3.GPIO_ModeDefaultEXTI=GPIO_MODE_IT_FALLING
PB3.GPIO_PuPd=GPIO_PULLUP
PB3.Signal=GPXTI3
PB6.GPIOParameters=GPIO_Label
PB6.GPIO_Label=SERVO1_HV
PB6.Mode=PWM Generation1 CH1N
PB6.Signal=TIM16_CH1N
PB7.GPIOParameters=GPIO_Label
PB7.GPIO_Label=SERVO2
PB7.Mode=PWM Generation1 CH1N
PB7.Signal=TIM17_CH1N
PB8.GPIOParameters=GPIO_Pu
PB8.GPIO_Pu=GPIO_PULLUP
PB8.Mode=I2C
PB8.Signal=I2C1_SCL
PB9.GPIOParameters=GPIO_Pu
PB9.GPIO_Pu=GPIO_PULLUP
PB9.Mode=I2C
PB9.Signal=I2C1_SDA
PC15-OSC32_OUT.GPIOParameters=GPIO_Label
PC15-OSC32_OUT.GPIO_Label=U_LED
PC15-OSC32_OUT.Signal=GPIO_Output
PF0-OSC_IN.Mode=HSE-External-Oscillator
PF0-OSC_IN.Signal=RCC_OSC_IN
PF1-OSC_OUT.Mode=HSE-External-Oscillator
PF1-OSC_OUT.Signal=RCC_OSC_OUT
RCC.SYSCLKFreq_VALUE=48000000
RCC.SYSCLKSource=RCC_SYSCLKSOURCE_PLLCLK
board=custom

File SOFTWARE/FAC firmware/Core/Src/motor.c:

/*
 * motor.c
 *
 *  Created on: Jul 7, 2024
 *      Author: Filippo Castellan
 */

#include "motor.h"
#include "DMApwm.h"

// select one of the following two type of driver
//#define DRIVER_IN_IN
#define DRIVER_PH_EN

extern uint16_t speed_steps;

extern uint8_t mLeft;
extern uint8_t mRight;
extern uint8_t mWeapon;

extern uint8_t m1Rev;
extern uint8_t m2Rev;
extern uint8_t m3Rev;

void initMotors() {
	initDMApwm();
}

void setTankMotor(TankMotors t) {
	// set the speed of the motors
	setMotorSpeedBidirectional(mLeft, t.speedL);
	setMotorSpeedBidirectional(mRight, t.speedR);
}

uint8_t getMotorRev(uint8_t motorN) {	// return 1 if the motorN is reversed, else 0
	uint8_t isRev = 0;
	switch (motorN) {
		case M1:
			isRev = m1Rev;
			break;
		case M2:
			isRev = m2Rev;
			break;
		case M3:
			isRev = m3Rev;
			break;
	}
	return isRev;
}

void setMotorSpeedBidirectional(uint8_t motorN, int16_t speed) {
	speed = calculateSpeedWithDeadZoneDouble(speed);
	speed = (speed - speed_steps / 2) * 2;
	uint16_t sp = abs(speed);
	sp = map(sp, 0, speed_steps, 0, MAX_DMA_PWM_VALUE);
	uint8_t dir;
	if (speed == 0) { // brake if speed is 0
		setDriverBrake(motorN);
		return;
	}
	if (speed >= 0)
		dir = TRUE;		// forward
	else
		dir = FALSE;	// backward

	if (getMotorRev(motorN)) dir = !dir;	//check if the motor is reversed, if it is reverse the direction

	setDriverSignals(motorN, sp, dir);
}

void setMotorSpeedUnidirectional(uint8_t motorN, int16_t speed) {
	uint16_t sp = calculateSpeedWithDeadZoneSingle(speed);
	uint8_t dir = m1Rev;
	if (speed == 0) {	// brake if speed is 0
		setDriverBrake(motorN);
		return;
	}
	if (getMotorRev(motorN)) dir = !dir;	//check if the motor is reversed, if it is reverse the direction

	setDriverSignals(motorN, sp, dir);
}

void setDriverSignals(uint8_t motorN, int16_t sp, uint8_t dir) {
#ifdef DRIVER_IN_IN
	switch (motorN) {
		case M1:
			if (dir == TRUE) {
				setDMApwmDuty(PWM_M1_B_GPIO_Port, PWM_M1_B_Pin, MAX_DMA_PWM_VALUE);
				setDMApwmDuty(PWM_M1_F_GPIO_Port, PWM_M1_F_Pin, MAX_DMA_PWM_VALUE - sp);
			} else {
				setDMApwmDuty(PWM_M1_B_GPIO_Port, PWM_M1_B_Pin, MAX_DMA_PWM_VALUE - sp);
				setDMApwmDuty(PWM_M1_F_GPIO_Port, PWM_M1_F_Pin, MAX_DMA_PWM_VALUE);
			}
			break;
		case M2:
			if (dir == TRUE) {
				setDMApwmDuty(PWM_M2_B_GPIO_Port, PWM_M2_B_Pin, MAX_DMA_PWM_VALUE);
				setDMApwmDuty(PWM_M2_F_GPIO_Port, PWM_M2_F_Pin, MAX_DMA_PWM_VALUE - sp);
			} else {
				setDMApwmDuty(PWM_M2_B_GPIO_Port, PWM_M2_B_Pin, MAX_DMA_PWM_VALUE - sp);
				setDMApwmDuty(PWM_M2_F_GPIO_Port, PWM_M2_F_Pin, MAX_DMA_PWM_VALUE);
			}
			break;
		case M3:
			if (dir == TRUE) {
				setDMApwmDuty(PWM_M3_B_GPIO_Port, PWM_M3_B_Pin, MAX_DMA_PWM_VALUE);
				setDMApwmDuty(PWM_M3_F_GPIO_Port, PWM_M3_F_Pin, MAX_DMA_PWM_VALUE - sp);
			} else {
				setDMApwmDuty(PWM_M3_B_GPIO_Port, PWM_M3_B_Pin, MAX_DMA_PWM_VALUE - sp);
				setDMApwmDuty(PWM_M3_F_GPIO_Port, PWM_M3_F_Pin, MAX_DMA_PWM_VALUE);
			}
			break;
	}
#endif

#ifdef DRIVER_PH_EN
	/*
	 * PA8 --> M1_PWM (PWM_M1_F) 	PA15 --> DIR_M1 (PWM_M1_B)
	 * PA9 --> M2_PWM (PWM_M2_F)	PA13 --> DIR_M2 (PWM_M2_B)
	 * PA10 --> M3_PWM (PWM_M3_F)	PA11 --> DIR_M3 (PWM_M3_B)
	 */
	switch (motorN) {
		case M1:
			if (dir) {	// set the direction
				setDMApwmDuty(PWM_M1_B_GPIO_Port, PWM_M1_B_Pin, MAX_DMA_PWM_VALUE);
			} else {
				setDMApwmDuty(PWM_M1_B_GPIO_Port, PWM_M1_B_Pin, 0);
			}
			setDMApwmDuty(PWM_M1_F_GPIO_Port, PWM_M1_F_Pin, sp);	// set the speed
			break;
		case M2:
			if (dir) {	// set the direction
				setDMApwmDuty(PWM_M2_B_GPIO_Port, PWM_M2_B_Pin, MAX_DMA_PWM_VALUE);
			} else {
				setDMApwmDuty(PWM_M2_B_GPIO_Port, PWM_M2_B_Pin, 0);
			}
			setDMApwmDuty(PWM_M2_F_GPIO_Port, PWM_M2_F_Pin, sp);	// set the speed
			break;
		case M3:
			if (dir) {	// set the direction
				setDMApwmDuty(PWM_M2_B_GPIO_Port, PWM_M3_B_Pin, MAX_DMA_PWM_VALUE);
			} else {
				setDMApwmDuty(PWM_M3_B_GPIO_Port, PWM_M3_B_Pin, 0);
			}
			setDMApwmDuty(PWM_M3_F_GPIO_Port, PWM_M3_F_Pin, sp);	// set the speed
			break;
	}
#endif
}

void setDriverBrake(uint8_t motorN) {
#ifdef DRIVER_IN_IN
	switch (motorN) {
		case M1:
			setDMApwmDuty(PWM_M1_B_GPIO_Port, PWM_M1_B_Pin, MAX_DMA_PWM_VALUE);
			setDMApwmDuty(PWM_M1_F_GPIO_Port, PWM_M1_F_Pin, MAX_DMA_PWM_VALUE);
			break;
		case M2:
			setDMApwmDuty(PWM_M2_B_GPIO_Port, PWM_M2_B_Pin, MAX_DMA_PWM_VALUE);
			setDMApwmDuty(PWM_M2_F_GPIO_Port, PWM_M2_F_Pin, MAX_DMA_PWM_VALUE);
			break;
		case M3:
			setDMApwmDuty(PWM_M3_B_GPIO_Port, PWM_M3_B_Pin, MAX_DMA_PWM_VALUE);
			setDMApwmDuty(PWM_M3_F_GPIO_Port, PWM_M3_F_Pin, MAX_DMA_PWM_VALUE);
			break;
	}
#endif

#ifdef DRIVER_PH_EN
	switch (motorN) {
		case M1:
			setDMApwmDuty(PWM_M1_F_GPIO_Port, PWM_M1_F_Pin, 0);
			break;
		case M2:
			setDMApwmDuty(PWM_M2_F_GPIO_Port, PWM_M2_F_Pin, 0);
			break;
		case M3:
			setDMApwmDuty(PWM_M3_F_GPIO_Port, PWM_M3_F_Pin, 0);
			break;
	}
#endif
}

/*	Calculate the speed with dead-zone for single direction DC motor and servos
 *  Center +-3, max -3, min +3
 *	change the deadzone value according your needs
 */
#define DEADZONE 10
int16_t calculateSpeedWithDeadZoneSingle(int16_t speed) {
	uint16_t returnValue = speed;
	if (speed > (speed_steps / 2 - DEADZONE) && speed < (speed_steps / 2 + DEADZONE)) returnValue = speed_steps / 2;// central deadzone
	if (speed < DEADZONE) returnValue = 0;	// lower deadzone
	if (speed > speed_steps - DEADZONE) returnValue = speed_steps;	// upper deadzone
	return returnValue;
}
/*	Calculate the speed with dead-zone for double direction DC motors
 *  max -3, min +3
 *	change the deadzone value according your needs
 */
int16_t calculateSpeedWithDeadZoneDouble(int16_t speed) {
	int16_t returnValue = speed;
	if (speed < DEADZONE) returnValue = 0;	// lower deadzone
	if (speed > speed_steps - DEADZONE) returnValue = speed_steps;	// upper deadzone
	return returnValue;
}

/*	This is a blocking function that causes the motors to beep,
 *  keeping the duration as short as possible.
 * @duration:
 *
 */
void makeSound(uint8_t motorN, uint8_t duration) {
	uint32_t time = HAL_GetTick();
	enableMotor(motorN);
	uint16_t sp = (MAX_DMA_PWM_VALUE / 100) * 2;
	while (HAL_GetTick() <= time + duration) {
#ifdef DRIVER_IN_IN
		switch (motorN) {
			case M1:
				setDMApwmDuty(PWM_M1_B_GPIO_Port, PWM_M1_B_Pin, MAX_DMA_PWM_VALUE);
				setDMApwmDuty(PWM_M1_F_GPIO_Port, PWM_M1_F_Pin, MAX_DMA_PWM_VALUE - sp);
				break;
			case M2:
				setDMApwmDuty(PWM_M2_B_GPIO_Port, PWM_M2_B_Pin, MAX_DMA_PWM_VALUE);
				setDMApwmDuty(PWM_M2_F_GPIO_Port, PWM_M2_F_Pin, MAX_DMA_PWM_VALUE - sp);
				break;
			case M3:
				setDMApwmDuty(PWM_M3_B_GPIO_Port, PWM_M3_B_Pin, MAX_DMA_PWM_VALUE);
				setDMApwmDuty(PWM_M3_F_GPIO_Port, PWM_M3_F_Pin, MAX_DMA_PWM_VALUE - sp);
				break;
		}
#endif

#ifdef DRIVER_PH_EN
		switch (motorN) {
			case M1:
				setDMApwmDuty(PWM_M1_B_GPIO_Port, PWM_M1_B_Pin, MAX_DMA_PWM_VALUE);
				setDMApwmDuty(PWM_M1_F_GPIO_Port, PWM_M1_F_Pin, sp);
				break;
			case M2:
				setDMApwmDuty(PWM_M2_B_GPIO_Port, PWM_M2_B_Pin, MAX_DMA_PWM_VALUE);
				setDMApwmDuty(PWM_M2_F_GPIO_Port, PWM_M2_F_Pin, sp);
				break;
			case M3:
				setDMApwmDuty(PWM_M3_B_GPIO_Port, PWM_M3_B_Pin, 1);
				setDMApwmDuty(PWM_M3_F_GPIO_Port, PWM_M3_F_Pin, sp);
				break;
		}
#endif
	}
	disableMotor(motorN);
}

void disableMotor(uint8_t motorN) {
	switch (motorN) {
		case M1:
			HAL_GPIO_WritePin(SLEEPN_M1_GPIO_Port, SLEEPN_M1_Pin, FALSE);
			break;
		case M2:
			HAL_GPIO_WritePin(SLEEPN_M2_GPIO_Port, SLEEPN_M2_Pin, FALSE);
			break;
		case M3:
			HAL_GPIO_WritePin(SLEEPN_M3_GPIO_Port, SLEEPN_M3_Pin, FALSE);
			break;
	}
}

void enableMotor(uint8_t motorN) {
	switch (motorN) {
		case M1:
			HAL_GPIO_WritePin(SLEEPN_M1_GPIO_Port, SLEEPN_M1_Pin, TRUE);
			break;
		case M2:
			HAL_GPIO_WritePin(SLEEPN_M2_GPIO_Port, SLEEPN_M2_Pin, TRUE);
			break;
		case M3:
			HAL_GPIO_WritePin(SLEEPN_M3_GPIO_Port, SLEEPN_M3_Pin, TRUE);
			break;
	}
}
